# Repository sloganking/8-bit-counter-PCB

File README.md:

# 8-bit counter PCB
 This repository holds an example 8-bit counter PCB designed in KiCad. This was my first PCB design and assembly so I made a simple 8 bit counter to get familiar with KiCad and the PCB assembly process.

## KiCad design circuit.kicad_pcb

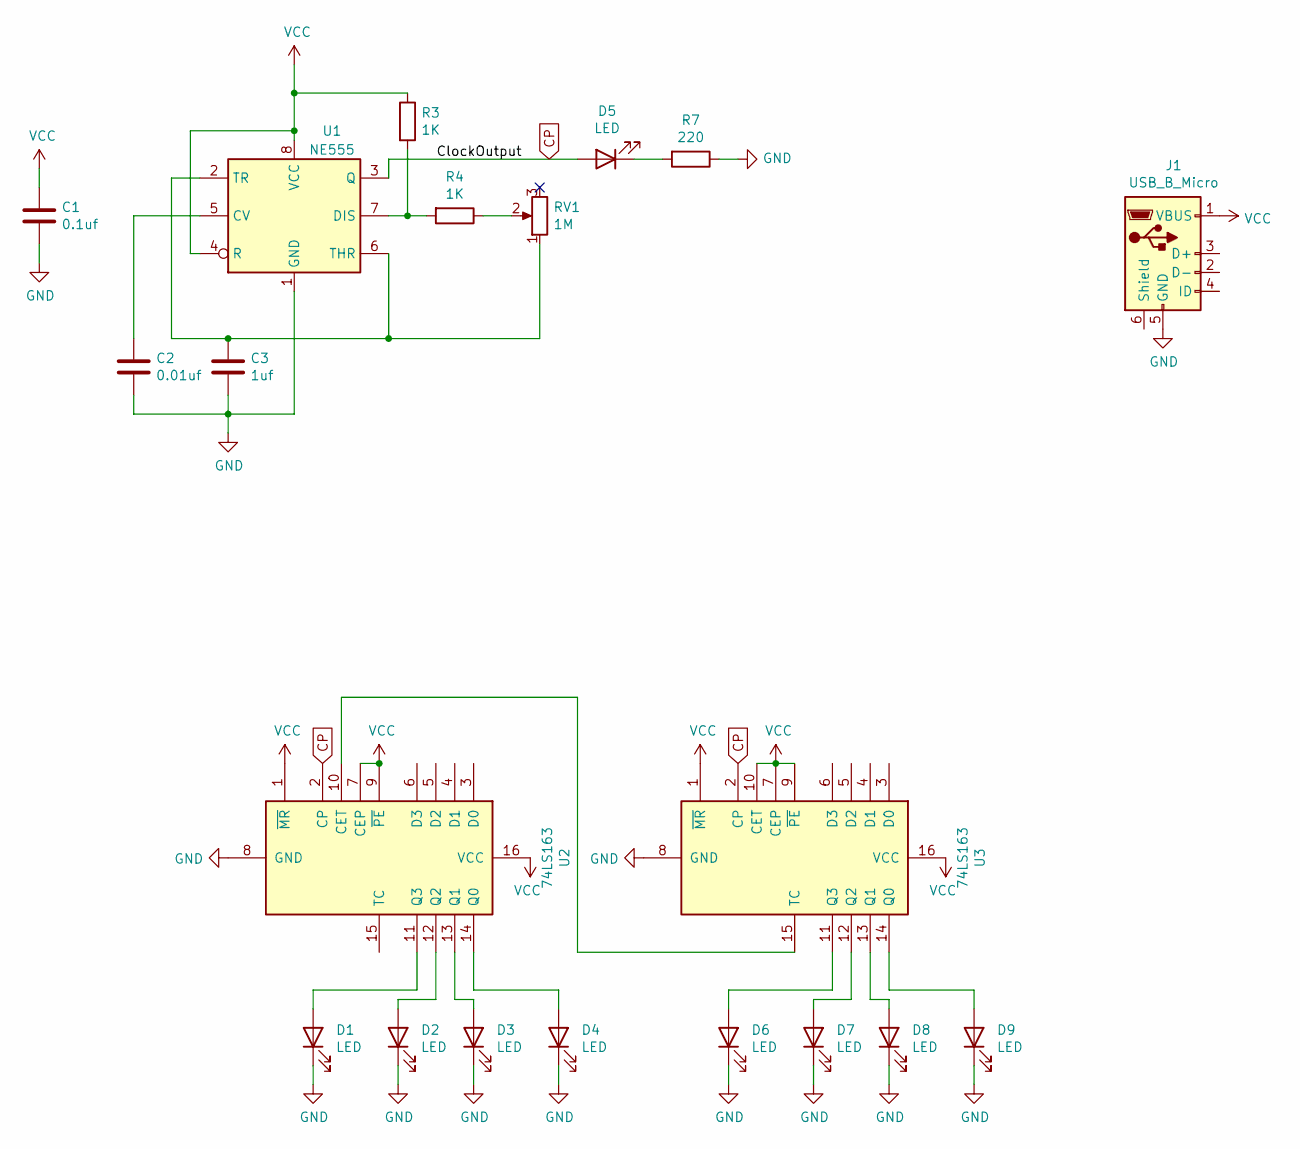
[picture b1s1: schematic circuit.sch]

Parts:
C1: 0.1uf; C_Disc_D4.3mm_W1.9mm_P5.00mm
C2: 0.01uf; C_Disc_D4.3mm_W1.9mm_P5.00mm
C3: 1uf; C_Disc_D4.3mm_W1.9mm_P5.00mm
D1, D2, D3, D4, D5, D6, D7, D8, D9: LED; LED_D3.0mm
J1: USB_B_Micro; PinHeader_1x06_P2.54mm_Vertical
R3, R4: 1K; R_Axial_DIN0207_L6.3mm_D2.5mm_P15.24mm_Horizontal
R7: 220; R_Axial_DIN0207_L6.3mm_D2.5mm_P15.24mm_Horizontal
RV1: 1M; Potentiometer_ACP_CA9-H5_Horizontal
U1: NE555; DIP-8_W7.62mm_LongPads
U2, U3: 74LS163; DIP-16_W7.62mm_LongPads

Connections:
CP: D5.2 (A), U1.3 (Q), U2.2 (CP), U3.2 (CP)
GND: C1.2, C2.2, C3.2, D1.1 (K), D2.1 (K), D3.1 (K), D4.1 (K), D6.1 (K), D7.1 (K), D8.1 (K), D9.1 (K), J1.5 (GND), R7.1, U1.1 (GND), U2.8 (GND), U3.8 (GND)
unnamed: C2.1, U1.5 (CV)
unnamed: C3.1, RV1.1, U1.2 (TR), U1.6 (THR)
unnamed: D1.2 (A), U2.11 (Q3)
unnamed: D2.2 (A), U2.12 (Q2)
unnamed: D3.2 (A), U2.13 (Q1)
unnamed: D4.2 (A), U2.14 (Q0)
unnamed: D5.1 (K), R7.2
unnamed: D6.2 (A), U3.11 (Q3)
unnamed: D7.2 (A), U3.12 (Q2)
unnamed: D8.2 (A), U3.13 (Q1)
unnamed: D9.2 (A), U3.14 (Q0)
unnamed: R3.2, R4.2, U1.7 (DIS)
unnamed: R4.1, RV1.2
unnamed: U2.10 (CET), U3.15 (TC)
VCC: C1.1, J1.1 (VBUS), R3.1, U1.4 (R), U1.8 (VCC), U2.1 (~MR), U2.7 (CEP), U2.9 (~PE), U2.16 (VCC), U3.1 (~MR), U3.7 (CEP), U3.9 (~PE), U3.10 (CET), U3.16 (VCC)

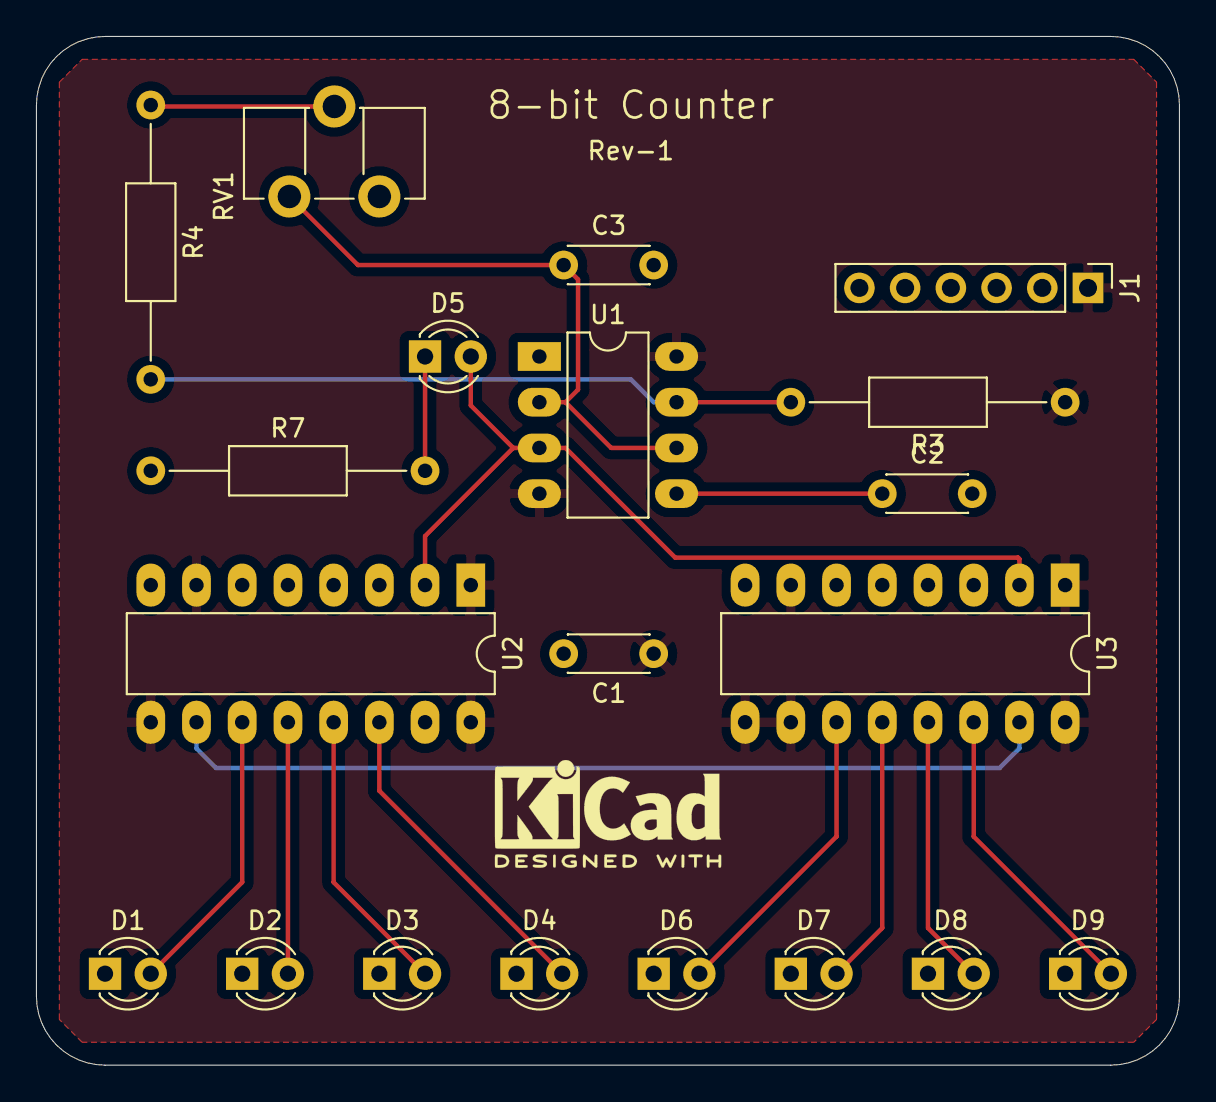
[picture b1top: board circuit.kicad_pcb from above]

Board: 2 copper layers, 63.5 x 57.2 mm, 20 parts (0 on the bottom side), 17 nets.

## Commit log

2020-06-12 added pictures
2020-06-12 fix images
